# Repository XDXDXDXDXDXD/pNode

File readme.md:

# pNode v2.0
## Installing Firmware
Make sure you have ```python``` and ```pip``` installed so that you can download and install ```esptool```
```
pip install esptool
```
Connect pNode to an FTDI chip via its USB port. The one we're using could be pruchased form sparkfun: https://www.sparkfun.com/products/9716

Restart pNode while pressing reset and the boot button on the back of the PCB until indicated by red LED. Once on, the pNode is in boot-loading mode, and it's ready for a new firmware update.

First, completely erase flash memory:
```
esptool.py --port /dev/cu.usbserial-A50285BI --baud 115200 erase_flash
```

Then, write firmware:

```
esptool.py --port /dev/cu.usbserial-A50285BI --baud 115200 write_flash -fm dio 0x00000 nodemcu-firmware-float.bin
```

Note: In case firmware image was lost, use the following custom builds generator here: https://nodemcu-build.com/ with the following options: **file, gpio, http, node, sjson, tmr, uart, wifi**
then flash the float binary to the nodemcu using the esptool command.

Next make sure you have ```node``` and ```npm``` installed on your system to be able to install ```nodemcu-tool```

```
sudo npm install nodemcu-tool -g
```

for more information on ```nodemcu-tool``` please check further documentation here: https://www.npmjs.com/package/nodemcu-tool

Reboot pNode and wait until system memory is cleared. You can monitor this process using ```nodemcu-tool``` terminal interface

```
nodemcu-tool terminal
```

Note that this repo's directory contains a .nodemcutool configuration file with the following settings:

```
{
    "baudrate": "115200",
    "port": "/dev/cu.usbserial-A50285BI",
    "optimize": true,
    "compile": false,
    "keeppath": false
}
```

Having this configuration file prevents the need of having ```port``` and ```baudrate``` added to every single ```nodemcu-tool``` command. Change the serial port settings based on your system's environment.

Tip: one quick way to figure out the serial port is by looking at the /dev directory on UNIX based systems while re-plugging the FTDI.

```
cd /dev
ls -all
```

## Configuration

The application architecure running on the pNode follows the nodemcu paradigm, it's been programmed using the lua scripting language. For more information about nodemcu and lua please check the following link: https://nodemcu.readthedocs.io/en/master/

Use the ```nodemcu-tool``` command to upload, download, and run ```.lua``` scripts on the pNode. First edit the config.lua script with the editor of your choice with your WiFi ssid and password. Next, make sure to give your device a name, and a key. Also make sure that the token field is empty.

Note: if you're registering a new device, make sure that the token field is empty, this is the only way a pNode can be registered to the database. After a device is added to the database, copy it's token and paste it back into the configuration file, then re-upload the configuration file, and you're all set.

For more information on the security mechanisms used to protect HTTP requests, please check the server's repo here: https://github.com/XDXDXDXDXDXD/pNode-Server

The following commands is used to upload ```.lua``` scripts onto your new device.

```
nodemcu-tool upload config.lua
```

To upload the rest of the files you can use the following script called ```./upload.sh```

make sure it's executable first, before running it.
```
sudo chmod +x upload.sh
```
If at any time you needed to download or remove a file from the pNode use the following

```
nodemcu-tool download config.lua
nodemcu-tool remove config.lua
```

Reboot node, and monitor it's activity using the ```nodemcu-tool``` terminal interface.

## Hardware

### PCB

the pNode is a custom fork of the Adafruit's open source HUZZAH ESP8266 Breakout based on the ESP-12 SMD version of the ESP8266. More resources to be found here: https://learn.adafruit.com/adafruit-huzzah-esp8266-breakout/overview

The PCB folder contains the schematics and pcb-layout done with eagle 8.1 as well as the build of material (BOM) and gerber files.

### Enclosure

The enclosure was designed using Fusion 360, then 3D printed with an original Prusa I3
MK3S 3D printer with  Galaxy Silver PLA under default settings. STL files included in Enclosure folder.

Fusion 360 Link here: https://a360.co/2N8dewv

## License

The MIT License (MIT)

Permission is hereby granted, free of charge, to any person obtaining a copy of this software and associated documentation files (the "Software"), to deal in the Software without restriction, including without limitation the rights to use, copy, modify, merge, publish, distribute, sublicense, and/or sell copies of the Software, and to permit persons to whom the Software is furnished to do so, subject to the following conditions:

The above copyright notice and this permission notice shall be included in all copies or substantial portions of the Software.

THE SOFTWARE IS PROVIDED "AS IS", WITHOUT WARRANTY OF ANY KIND, EXPRESS OR IMPLIED, INCLUDING BUT NOT LIMITED TO THE WARRANTIES OF MERCHANTABILITY, FITNESS FOR A PARTICULAR PURPOSE AND NONINFRINGEMENT. IN NO EVENT SHALL THE AUTHORS OR COPYRIGHT HOLDERS BE LIABLE FOR ANY CLAIM, DAMAGES OR OTHER LIABILITY, WHETHER IN AN ACTION OF CONTRACT, TORT OR OTHERWISE, ARISING FROM, OUT OF OR IN CONNECTION WITH THE SOFTWARE OR THE USE OR OTHER DEALINGS IN THE SOFTWARE.

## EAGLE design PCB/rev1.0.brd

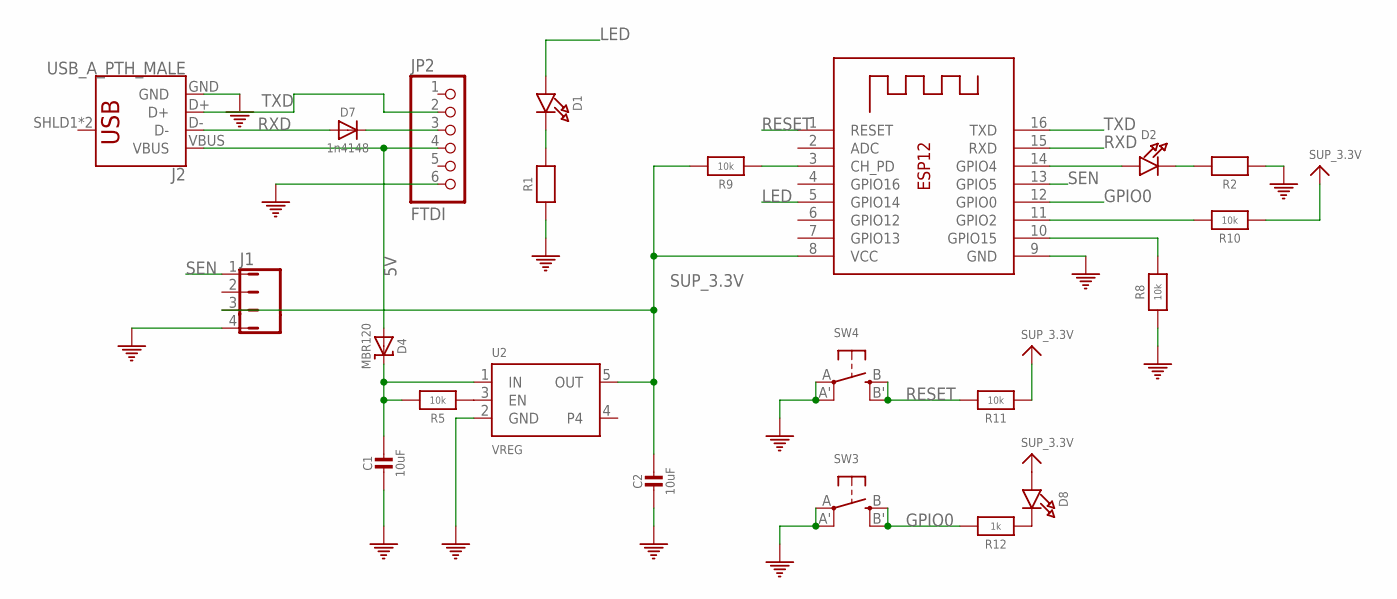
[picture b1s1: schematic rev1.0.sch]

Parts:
C1, C2: 10uF; 0805-NO
D1, D2, D8: LED0805_NOOUTLINE; CHIPLED_0805_NOOUTLINE
D4: MBR120; SOD-123
D7: 1n4148; SOD-323
J1: JMP/4P/SIP
J2: USB_A_PTH_MALE; USB-A-H
JP2: FTDI; 1X06_ROUND_70
R1, R2: RESISTOR0805_NOOUTLINE; 0805-NO
R5, R8, R9, R10, R11: 10k; 0805-NO
R12: 1k; 0805-NO
SW3, SW4: SWITCH_TACT_SMT4.6X2.8; BTN_KMR2_4.6X2.8
U2: VREG; SOT23-5
X1: ESP-12

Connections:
5V: D4.A, J2.VBUS, JP2.4
GND: C1.2, C2.2, J1.4, J2.GND, JP2.6, R1.1, R2.1, R8.1, SW3.A, SW3.A' (P1), SW4.A, SW4.A' (P1), U2.2 (GND), X1.9 (GND)
GPIO0: R12.2, SW3.B (S), SW3.B' (S1), X1.12 (GPIO0)
GPIO15: R8.2, X1.10 (GPIO15)
LED: D1.A, X1.5 (GPIO14)
unnamed: D1.C, R1.2
unnamed: D2.A, X1.14 (GPIO4)
unnamed: D8.C, R12.1
unnamed: R5.1, U2.3 (EN)
unnamed: D7.C, JP2.3
unnamed: C1.1, D4.C, R5.2, U2.1 (IN)
unnamed: D2.C, R2.2
unnamed: R10.2, X1.11 (GPIO2)
unnamed: R9.1, X1.3 (CH_PD)
RESET: R11.2, SW4.B (S), SW4.B' (S1), X1.1 (RESET)
RXD: D7.A, J2.D-, X1.15 (RXD)
SEN: J1.1, X1.13 (GPIO5)
SUP_3.3V: C2.1, D8.A, J1.3, R9.2, R10.1, R11.1, U2.5 (OUT), X1.8 (VCC)
TXD: J2.D+, JP2.2, X1.16 (TXD)

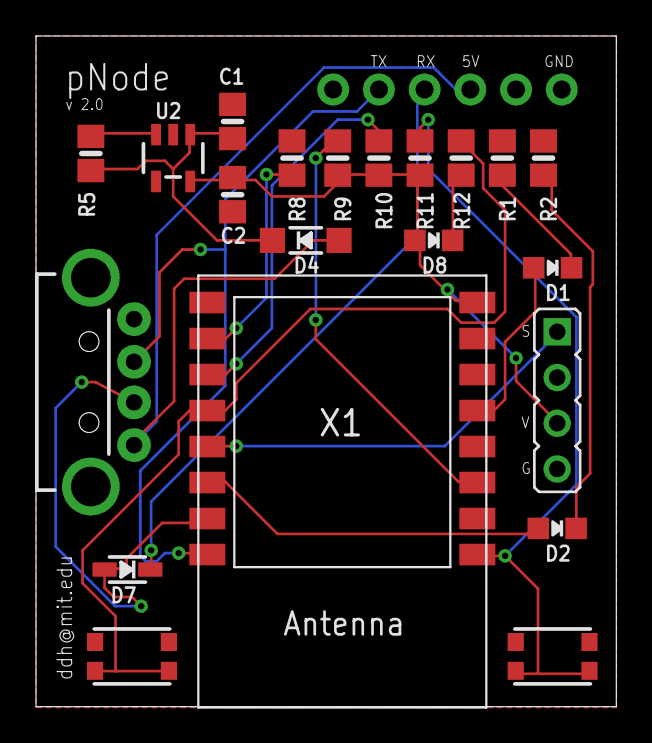
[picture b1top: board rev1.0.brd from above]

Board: 2 copper layers, 32.2 x 37.3 mm, 22 parts (0 on the bottom side), 19 nets.

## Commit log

2019-06-25 new repo
2019-06-25 adding license
2019-06-25 adding server's repo

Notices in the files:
parts and their libraries:
SparkFun-Connectors: Licensing: Creative Commons ShareAlike 4.0 International - https://creativecommons.org/licenses/by-sa/4.0
